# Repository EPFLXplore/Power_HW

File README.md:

# ERC_POWER_HW

This repository contains the KiCad design files for the power boards of the rover. The associated software can be found on the [ERC_POWER_SW](https://github.com/EPFLXplore/ERC_POWER_SW) repository.

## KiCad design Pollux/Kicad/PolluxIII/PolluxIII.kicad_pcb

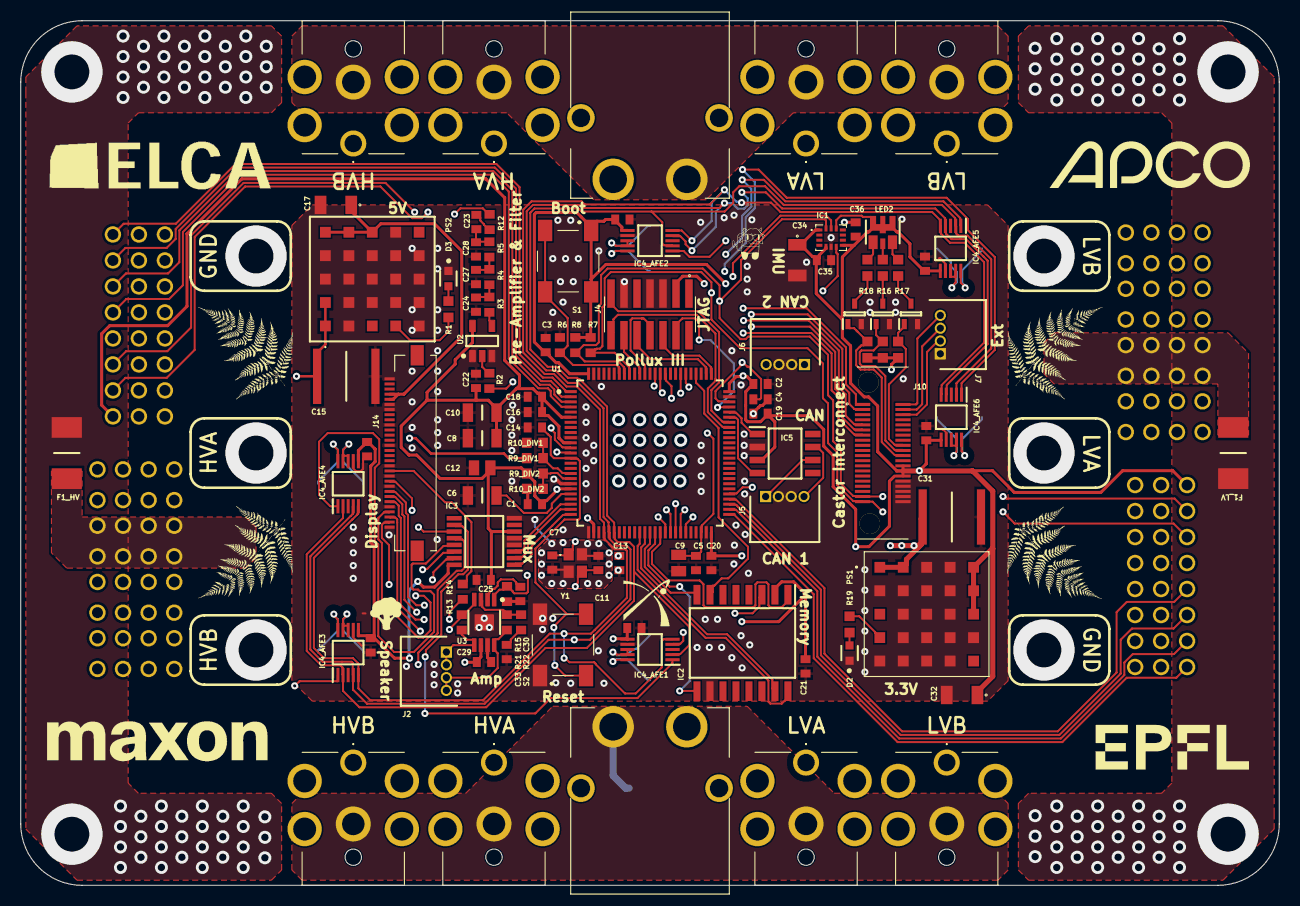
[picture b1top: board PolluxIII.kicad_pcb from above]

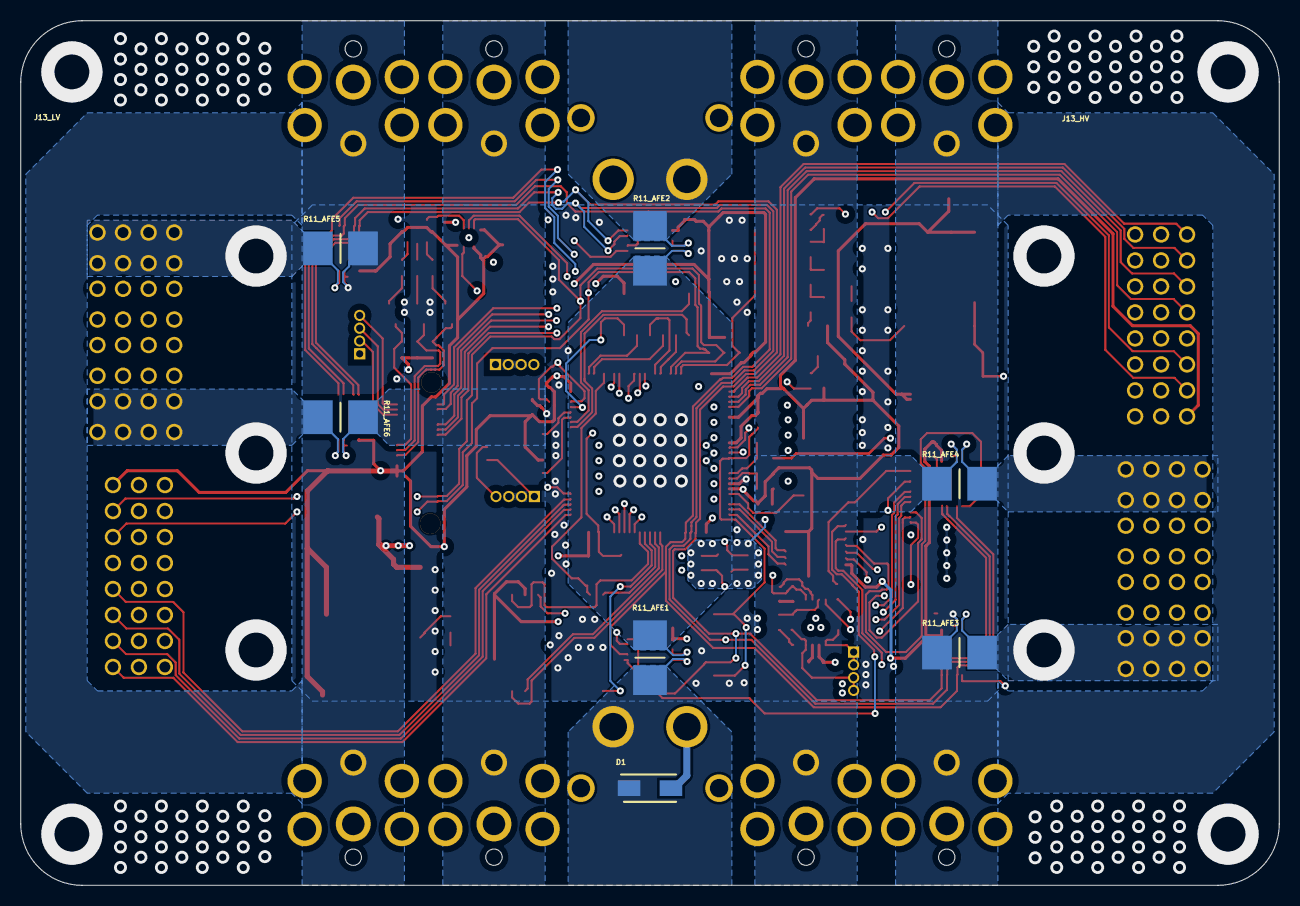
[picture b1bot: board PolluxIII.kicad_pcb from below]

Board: 4 copper layers, 123.0 x 84.5 mm, 118 parts (9 on the bottom side), 105 nets.

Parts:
C1, C2, C3, C4, C5, C13, C14, C16, C18, C19, C20, C21, C22, C25, C26_AFE1, C26_AFE2, C26_AFE3, C26_AFE4, C26_AFE5, C26_AFE6, C36: C0603C104K5RACTU; CAPC1608X95N
C6, C8, C10: C1206C105M5RECTU; CAPC3216X130N
C7, C11: CBR06C569B5GAC; CAPC1608X87N
C9: C0805C225K4REC7210; CAPC2012X140N
C12: C0805C475M4PACTU; CAPC2012X140N
C15, C31: C5750JB2A475M230KA; CAPC5750X310N
C17, C32: C1206C106K4RACTU; C1206
C23, C33: C0603C474K4PACTU; CAPC1608X95N
C24, C27, C28: C0603C472J5RACTU; CAPC1608X95N
C29: C0603C105K4RACTU; CAPC1608X95N
C30: C0603C224K8RAC7411; CAPC1608X95N
C34: C1206J225J4RACAUTO; C1206
C35: C0603C103K5RACTU; CAPC1608X95N
D1: BZG03C33-HM3-08; DIOM5127X229N
D2, D3: LS L29K-G1J2-1-Z; FP-LS_L29K-MFG
F1_HV, F1_LV: 0451020.MRL; FUSC6127X294N
IC1: ICM-42670-P; ICM42670P
IC2: MT25QL512ABB8ESF-0AAT; SOIC127P1032X265-16N
IC3: CD74HC137PWR; SOP65P640X120-16N
IC4_AFE1, IC4_AFE2, IC4_AFE3, IC4_AFE4, IC4_AFE5, IC4_AFE6: INA239AQDGSRQ1; SOP50P490X110-10N
IC5: SN65HVD232QDR; SOIC127P600X175-8N
J1, J3: XT60PW-M; XT60PWM
J2, J5, J6, J7: 53048-0450; SHDRRA4W35P0X125_1X4_675X550X350P
J4: FTSH-107-01-F-DV; FTSH-107-XX-YYY-DV
J10: ERF5-020-07.0-L-DV-K-TR; ERF5-020-XX.X-Y-DV-K-TR
J12_PWR1A1, J12_PWR1A2, J12_PWR1B1, J12_PWR1B2, J12_PWR2A1, J12_PWR2A2, J12_PWR2B1, J12_PWR2B2: PJ-082BH; PJ082BH
J13_HV, J13_LV: 46562-3001; 465623001
J14: 505110-3091; 5051103091
LED2: KRTBDWLM; KRTBDWLM3232T4U6JWAAABJ3R4S65V
PS1: RPMB3.3-3.0; RPMB5030
PS2: RPMB5.0-2.0; RPMB5020
Q5_LED_ST_B, Q5_LED_ST_G, Q5_LED_ST_R: DMN2004WK-7; SOT65P210X110-3N
R1, R19: CRCW06031K00JNEAC; RESC1608X55N
R2, R14: CRCW060333R0JNEAC; RESC1608X50N
R3, R4, R5: CRCW06031K00FKECC; RESC1608X50N
R6, R7, R8: CRCW06032K00JNEB; RESC1608X50N
R9_DIV1, R9_DIV2: TNPW0603100KBEEA; RESC1608X55N
R10_DIV1, R10_DIV2: TNPW06033K00BEEA; RESC1608X55N
R11_AFE1, R11_AFE2, R11_AFE3, R11_AFE4, R11_AFE5, R11_AFE6: PCS2512FR0010ET; RESC6430X90N
R12, R22: CRCW060310K2FKEA; RESC1608X50N
R13, R21: CRCW060320K0FKEAC; RESC1608X50N
R15: CRCW060347K0FKEAC; RESC1608X50N
R16: CRCW060320R0FKEAC; RESC1608X55N
R17, R18: CRCW060310R0JNEAC; RESC1608X55N
R20_LED_ST_B, R20_LED_ST_G, R20_LED_ST_R: CRCW060349K9FKEAC; RESC1608X55N
S1: BOOT; LL3301FF065QJ
S2: RESET; LL3301FF065QJ
U1: STM32H750VBT6; FP-LQFP100-1L-MFG
U2: SN74LVC1G125DBVR; DBV0005A_M
U3: TPA6205A1DGN; DGN0008D_N
Y1: NX3225SA-30.000M-STD-CSR-3; NX2520SA192MHzEXS00ACS05400

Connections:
3V3: C1.1, C2.1, C3.1, C8.2, C10.2, C12.1, C13.1, C16.1, C18.1, C19.1, C20.1, C21.1, C22.1, C25.1, C26_AFE1.2, C26_AFE2.2, C26_AFE3.2, C26_AFE4.2, C26_AFE5.2, C26_AFE6.2, C29.1, C32.1, C34.1, C35.1, C36.1, IC1.1, IC1.5, IC1.8, IC1.12, IC2.2, IC3.6, IC3.16, IC4_AFE1.6, IC4_AFE2.6, IC4_AFE3.6, IC4_AFE4.6, IC4_AFE5.6, IC4_AFE6.6, IC5.3, J4.3, J10.26, J10.28, J10.30, J13_HV.S17, J13_LV.S17, LED2.1, LED2.2, LED2.3, LED2.7, LED2.8, PS1.A5, PS1.B5, PS1.C5, R7.1, R8.1, R9_DIV2.1, R20_LED_ST_B.1, R20_LED_ST_G.1, R20_LED_ST_R.1, S1.1, S1.2, U1.6, U1.11, U1.20, U1.27, U1.50, U1.75, U1.100, U2.5, U3.6
+5: C17.1, J14.26, J14.27, PS2.A5, PS2.B5, PS2.C5
A1_C: J13_LV.S21, U1.54
A1_S: J13_LV.S23, U1.52
A2_C: J13_HV.S21, U1.4
A2_S: J13_HV.S23, U1.2
APD: J14.12, R14.1
APWM: J14.10, R2.1
B1_C: J13_LV.S22, U1.53
B1_S: J13_LV.S24, U1.51
B2_C: J13_HV.S22, U1.3
B2_S: J13_HV.S24, U1.1
BOOT: R6.2, S1.3, S1.4, U1.94
BYPASS: C30.2, U3.2
CANH: IC5.7, J5.4, J6.4
CANL: IC5.6, J5.1, J6.1
CAN_RX: IC5.4, U1.70
CAN_TX: IC5.1, U1.71
CAP: C4.1, C5.1, C9.2, U1.48, U1.73
CS1: IC3.15, IC4_AFE6.1
CS2: IC3.14, IC4_AFE5.1
CS3: IC3.13, IC4_AFE4.1
CS4: IC3.12, IC4_AFE3.1
CS5: IC3.11, IC4_AFE2.1
CS6: IC3.10, IC4_AFE1.1
DCS: J14.4, U1.41
DINT: J14.3, U1.45
DMISO: J14.7, U1.43
DMOSI: J14.6, U1.44
DRX: J4.13, U1.69
DSCK: J14.8, U1.42
DTX: J4.14, U1.68
FSYNC: IC1.7, U1.55
GND: C1.2, C2.2, C3.2, C4.2, C5.2, C6.1, C7.1, C8.1, C9.1, C10.1, C11.1, C12.2, C13.2, C14.2, C15.2, C16.2, C17.2, C18.2, C19.2, C20.2, C21.2, C22.2, C24.2, C25.2, C26_AFE1.1, C26_AFE2.1, C26_AFE3.1, C26_AFE4.1, C26_AFE5.1, C26_AFE6.1, C27.2, C28.2, C29.2, C30.1, C31.2, C32.2, C33.1, C34.2, C35.2, C36.2, D1.2, D2.1, D3.1, IC1.6, IC2.10, IC3.4, IC3.5, IC3.8, IC4_AFE1.7, IC4_AFE2.7, IC4_AFE3.7, IC4_AFE4.7, IC4_AFE5.7, IC4_AFE6.7, IC5.2, J1.2, J3.2, J4.5, J4.7, J4.11, J5.2, J5.3, J6.2, J6.3, J7.1, J10.32, J10.34, J10.36, J10.38, J10.40, J12_PWR1A1.2, J12_PWR1A2.2, J12_PWR1B1.2, J12_PWR1B2.2, J12_PWR2A1.2, J12_PWR2A2.2, J12_PWR2B1.2, J12_PWR2B2.2, J13_HV.P2, J13_HV.S20, J13_LV.P2, J13_LV.S20, J14.1, J14.5, J14.9, J14.11, J14.13, J14.17, J14.21, J14.24, J14.25, J14.30, PS1.A3, PS1.A4, PS1.B1, PS1.B2, PS1.B3, PS1.B4, PS1.C2, PS1.C3, PS1.C4, PS1.D2, PS1.D3, PS1.D4, PS1.D5, PS1.E1, PS1.E2, PS1.E3, PS1.E4, PS2.A3, PS2.A4, PS2.B1, PS2.B2, PS2.B3, PS2.B4, PS2.C2, PS2.C3, PS2.C4, PS2.D2, PS2.D3, PS2.D4, PS2.D5, PS2.E1, PS2.E2, PS2.E3, PS2.E4, Q5_LED_ST_B.2, Q5_LED_ST_G.2, Q5_LED_ST_R.2, R6.1, R10_DIV1.2, R10_DIV2.2, R15.1, S2.1, S2.2, U1.10, U1.19, U1.26, U1.49, U1.74, U1.99, U2.1, U2.3, U3.7, U3.9, Y1.2, Y1.4
GPIO0: J7.4, J10.2
GPIO1: J7.3, J10.4
GPIO2: J7.2, J10.6
HSE_IN: C7.2, U1.12, Y1.1
HSE_OUT: C11.2, U1.13, Y1.3
HVA: IC4_AFE4.10, J13_HV.P4, R11_AFE4.1
HVB: IC4_AFE3.10, J13_HV.P1, R11_AFE3.1
JTCK: J4.6, U1.76
JTDI: J4.10, U1.77
JTDO: J4.8, U1.89
JTMS: J4.4, U1.72
JTRST: J4.12, U1.90
LVA: IC4_AFE6.10, J13_LV.P4, R11_AFE6.1
LVB: IC4_AFE5.10, J13_LV.P1, R11_AFE5.1
MISO: IC4_AFE1.4, IC4_AFE2.4, IC4_AFE3.4, IC4_AFE4.4, IC4_AFE5.4, IC4_AFE6.4, U1.30
MOSI: IC4_AFE1.2, IC4_AFE2.2, IC4_AFE3.2, IC4_AFE4.2, IC4_AFE5.2, IC4_AFE6.2, U1.31
NRST: C14.1, IC2.3, J14.2, S2.3, S2.4, U1.14
NetC6_2: C6.2, U1.21
NetC23_1: C23.1, R12.1
NetC23_2: C23.2, C28.1, R5.1
NetC24_1: C24.1, R3.1, R4.2
NetC27_1: C27.1, R4.1, R5.2
NetC33_2: C33.2, R22.2
NetD2_2: D2.2, R19.1
NetD3_2: D3.2, R1.1
NetF1_HV_2: F1_HV.2, J13_HV.P3
NetF1_LV_2: F1_LV.2, J13_LV.P3
NetJ2_1: J2.1, J2.2, R13.1, U3.5
NetJ2_3: J2.3, J2.4, R21.1, U3.8
NetJ10_18: J10.18, Q5_LED_ST_G.1, R20_LED_ST_G.2
NetJ10_20: J10.20, Q5_LED_ST_R.1, R20_LED_ST_R.2
NetJ10_22: J10.22, Q5_LED_ST_B.1, R20_LED_ST_B.2
NetLED2_4: LED2.4, R18.2
NetLED2_5: LED2.5, R16.2
NetLED2_6: LED2.6, R17.2
NetPS1_D1: PS1.D1, R19.2
NetPS2_D1: PS2.D1, R1.2
NetQ5_LED_ST_B_3: Q5_LED_ST_B.3, R18.1
NetQ5_LED_ST_G_3: Q5_LED_ST_G.3, R17.1
NetQ5_LED_ST_R_3: Q5_LED_ST_R.3, R16.1
NetR2_2: R2.2, U2.2
NetR3_2: R3.2, U2.4
NetR9_DIV1_2: R9_DIV1.2, R10_DIV1.1, U1.17
NetR9_DIV2_2: R9_DIV2.2, R10_DIV2.1, U1.18
NetR12_2: R12.2, R13.2, U3.4
NetR21_2: R21.2, R22.1, U3.3
OHVA: IC4_AFE4.8, IC4_AFE4.9, J12_PWR2A1.1, J12_PWR2A2.1, R11_AFE4.2
OHVB: IC4_AFE3.8, IC4_AFE3.9, J12_PWR2B1.1, J12_PWR2B2.1, R11_AFE3.2
OLVA: IC4_AFE6.8, IC4_AFE6.9, J12_PWR1A1.1, J12_PWR1A2.1, R11_AFE6.2
OLVB: IC4_AFE5.8, IC4_AFE5.9, J12_PWR1B1.1, J12_PWR1B2.1, R11_AFE5.2
QSPI0: IC2.15, U1.37
QSPI1: IC2.8, U1.38
QSPI2: IC2.9, U1.39
QSPI3: IC2.1, U1.40
QSPICK: IC2.16, U1.36
QSPICS: IC2.7, U1.79
SBUS0: J10.1, U1.86
SBUS1: J10.3, U1.87
SBUS4: J10.9, U1.85
SBUS5: J10.11, U1.81
SBUS6: J10.13, U1.82
SCK: IC4_AFE1.5, IC4_AFE2.5, IC4_AFE3.5, IC4_AFE4.5, IC4_AFE5.5, IC4_AFE6.5, U1.29
SCL: IC1.13, J10.39, J13_HV.S19, J13_LV.S19, R7.2, U1.92
SDA: IC1.14, J10.37, J13_HV.S18, J13_LV.S18, R8.2, U1.93
SPI_A0: IC3.1, U1.25
SPI_A1: IC3.2, U1.24
SPI_A2: IC3.3, U1.23
V_BAT: D1.1, IC4_AFE1.10, J1.1, R11_AFE1.1
V_IN: C15.1, C31.1, F1_HV.1, F1_LV.1, IC4_AFE1.8, IC4_AFE1.9, IC4_AFE2.10, PS1.A1, PS1.A2, PS2.A1, PS2.A2, R9_DIV1.1, R11_AFE1.2, R11_AFE2.1
V_OUT: IC4_AFE2.8, IC4_AFE2.9, J3.1, R11_AFE2.2
nSHDN: R14.2, R15.2, U3.1

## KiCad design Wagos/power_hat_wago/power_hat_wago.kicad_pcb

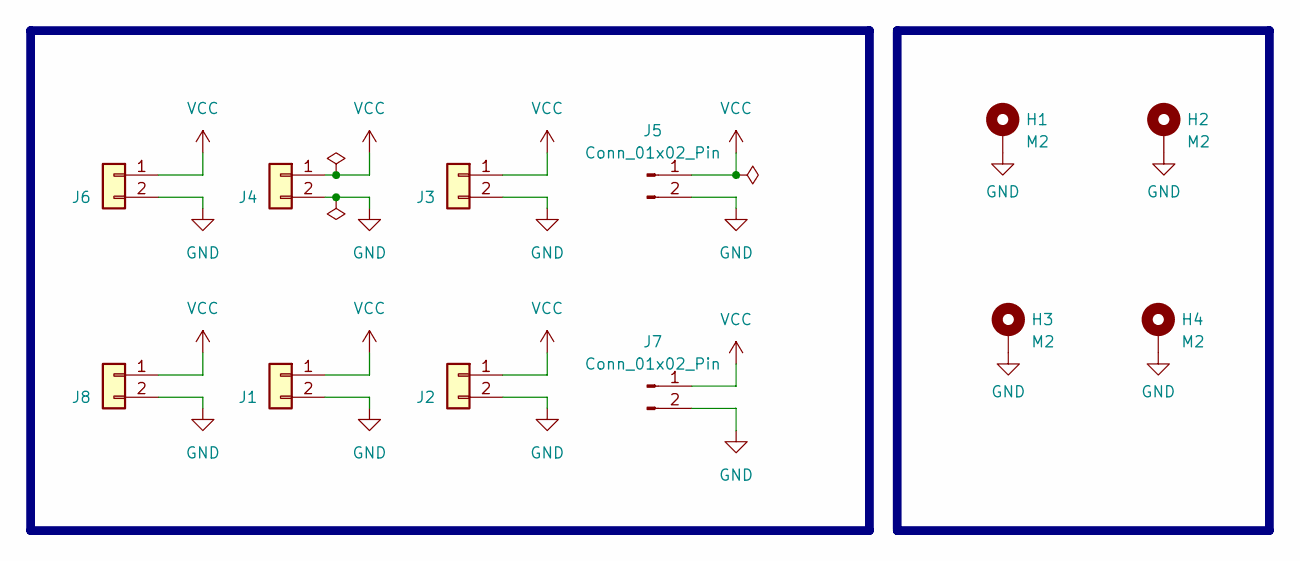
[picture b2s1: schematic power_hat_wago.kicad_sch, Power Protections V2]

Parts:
H1, H2, H3, H4: M2; MountingHole_3.2mm_M3_Pad_Via
J1, J2, J3, J4, J6, J8: XT30PW-M/Terminal block; AMASS_XT30PW-M_1x02_P2.50mm_Horizontal; Manufacturer_Part_Number XT30PW-M
J5: Conn_01x02_Pin; AMASS_XT60PW-M_1x02_P7.20mm_Horizontal
J7: Conn_01x02_Pin; AMASS_XT60PW-F_1x02_P7.20mm_Horizontal

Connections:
GND: H1.1 (1_1), H2.1 (1_1), H3.1 (1_1), H4.1 (1_1), J1.2, J2.2, J3.2, J4.2, J5.2, J6.2, J7.2, J8.2
VCC: J1.1, J2.1, J3.1, J4.1, J5.1, J6.1, J7.1, J8.1

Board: 4 copper layers, 12 parts (0 on the bottom side), 2 nets, no tracks yet.

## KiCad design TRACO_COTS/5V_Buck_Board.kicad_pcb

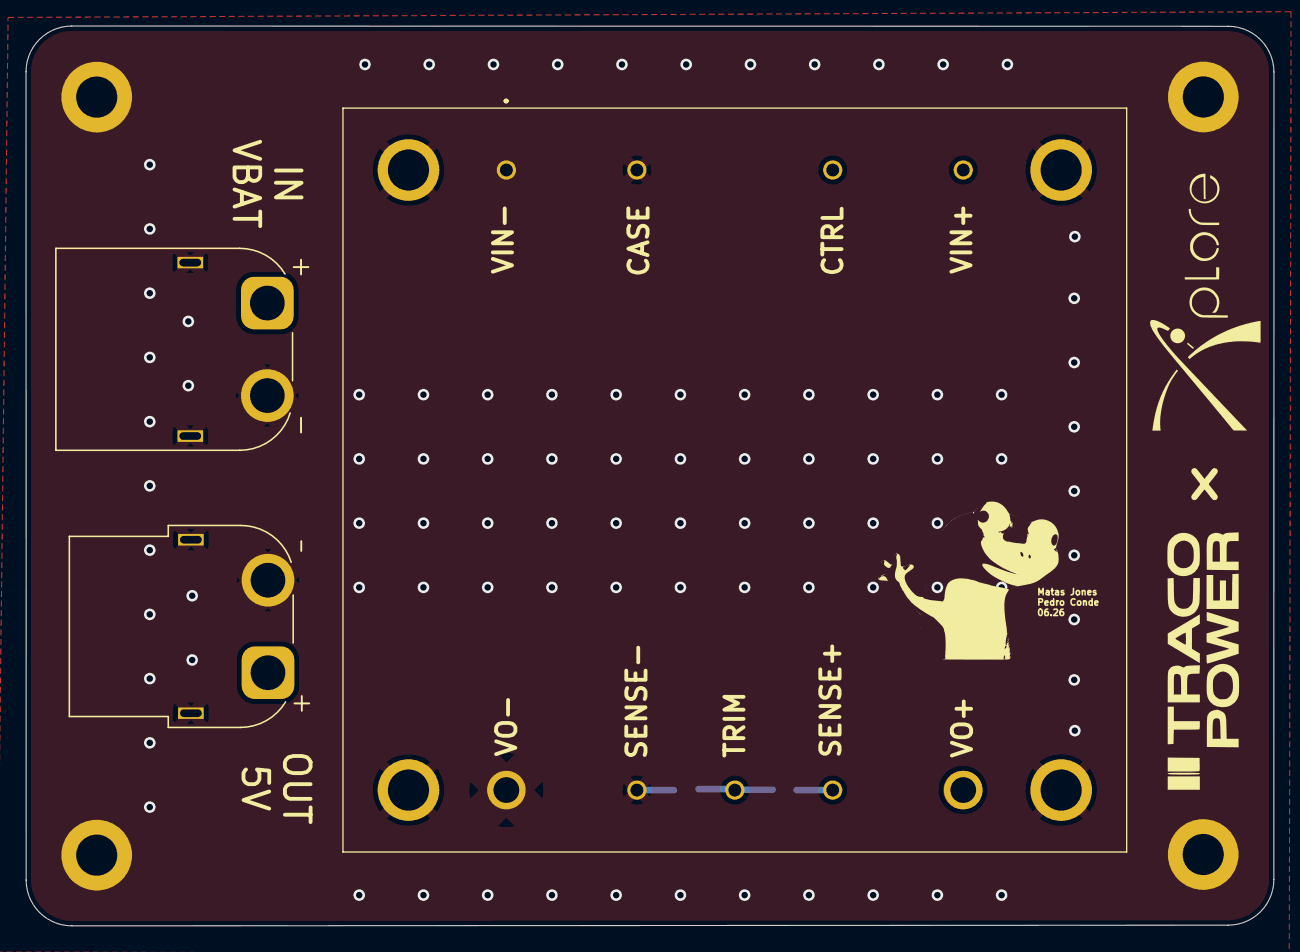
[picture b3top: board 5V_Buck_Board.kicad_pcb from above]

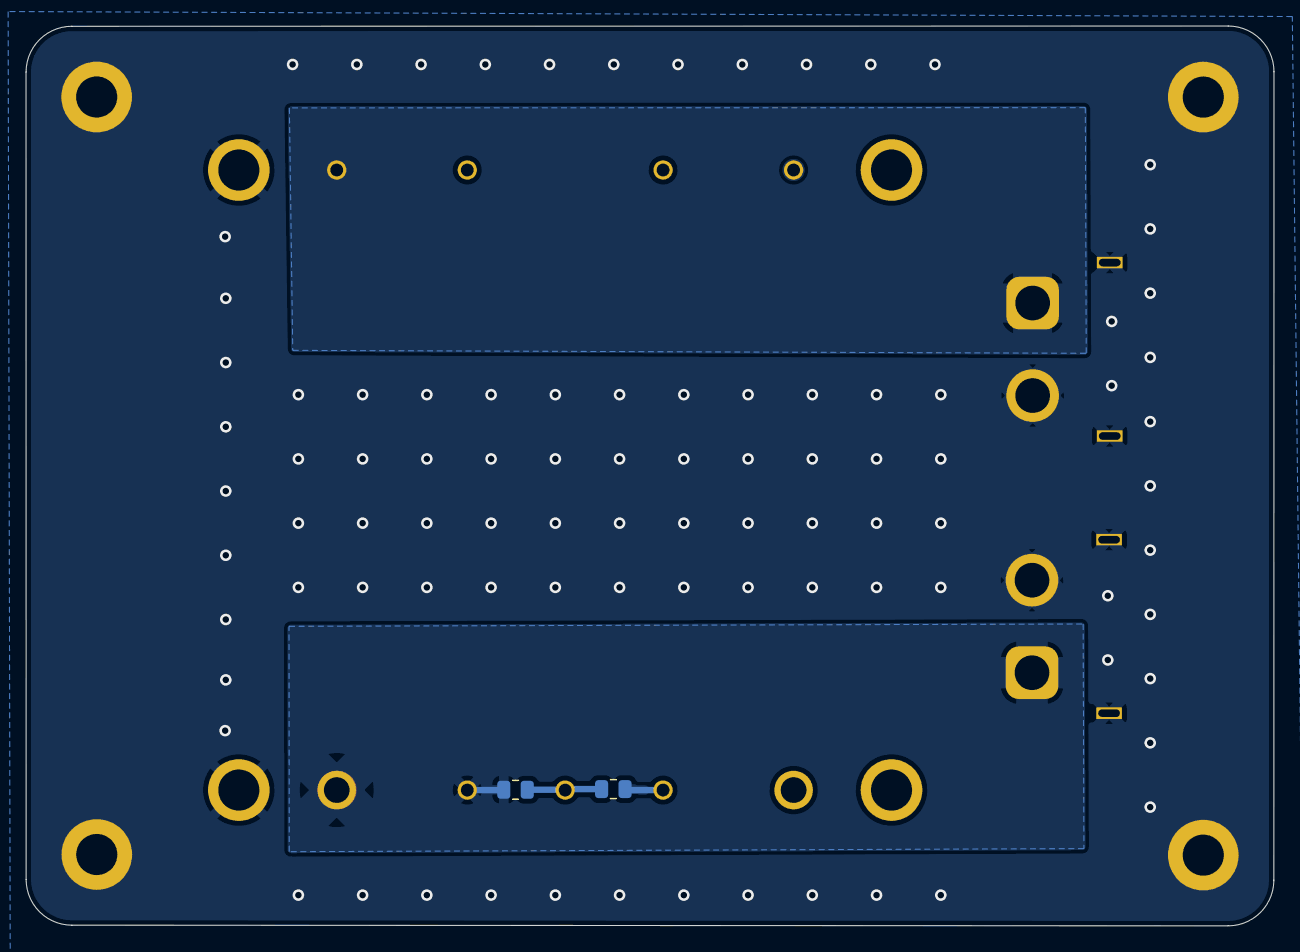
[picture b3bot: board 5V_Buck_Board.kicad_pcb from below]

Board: 2 copper layers, 97.1 x 70.0 mm, 9 parts (2 on the bottom side), 4 nets.

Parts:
H1, H2, H3, H4: MountingHole_Pad; MountingHole_3.2mm_M3_ISO14580_Pad
J1: XT60PW-M; AMASS_XT60PW-M_1x02_P7.20mm_Horizontal
J2: XT60PW-F; AMASS_XT60PW-F_1x02_P7.20mm_Horizontal
PS1: TEP_100-2411WIR; TEP1002411WIR
R1, R2: NM; R_0805_2012Metric

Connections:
GND: H1.1, H2.1, H3.1, H4.1, J1.2, J1.MH1, J1.MH2, J2.2, J2.MH1, J2.MH2, PS1.1 (-VIN(GND)), PS1.2 (CASE), PS1.5 (-VOUT), PS1.6 (-SENSE), PS1.MH1, PS1.MH2, PS1.MH3, PS1.MH4, R2.2
unnamed: J2.1, PS1.8 (+SENSE), PS1.9 (+VOUT), R1.1
unnamed: J1.1, PS1.4 (+VIN(VCC))
unnamed: PS1.7 (TRIM), R1.2, R2.1

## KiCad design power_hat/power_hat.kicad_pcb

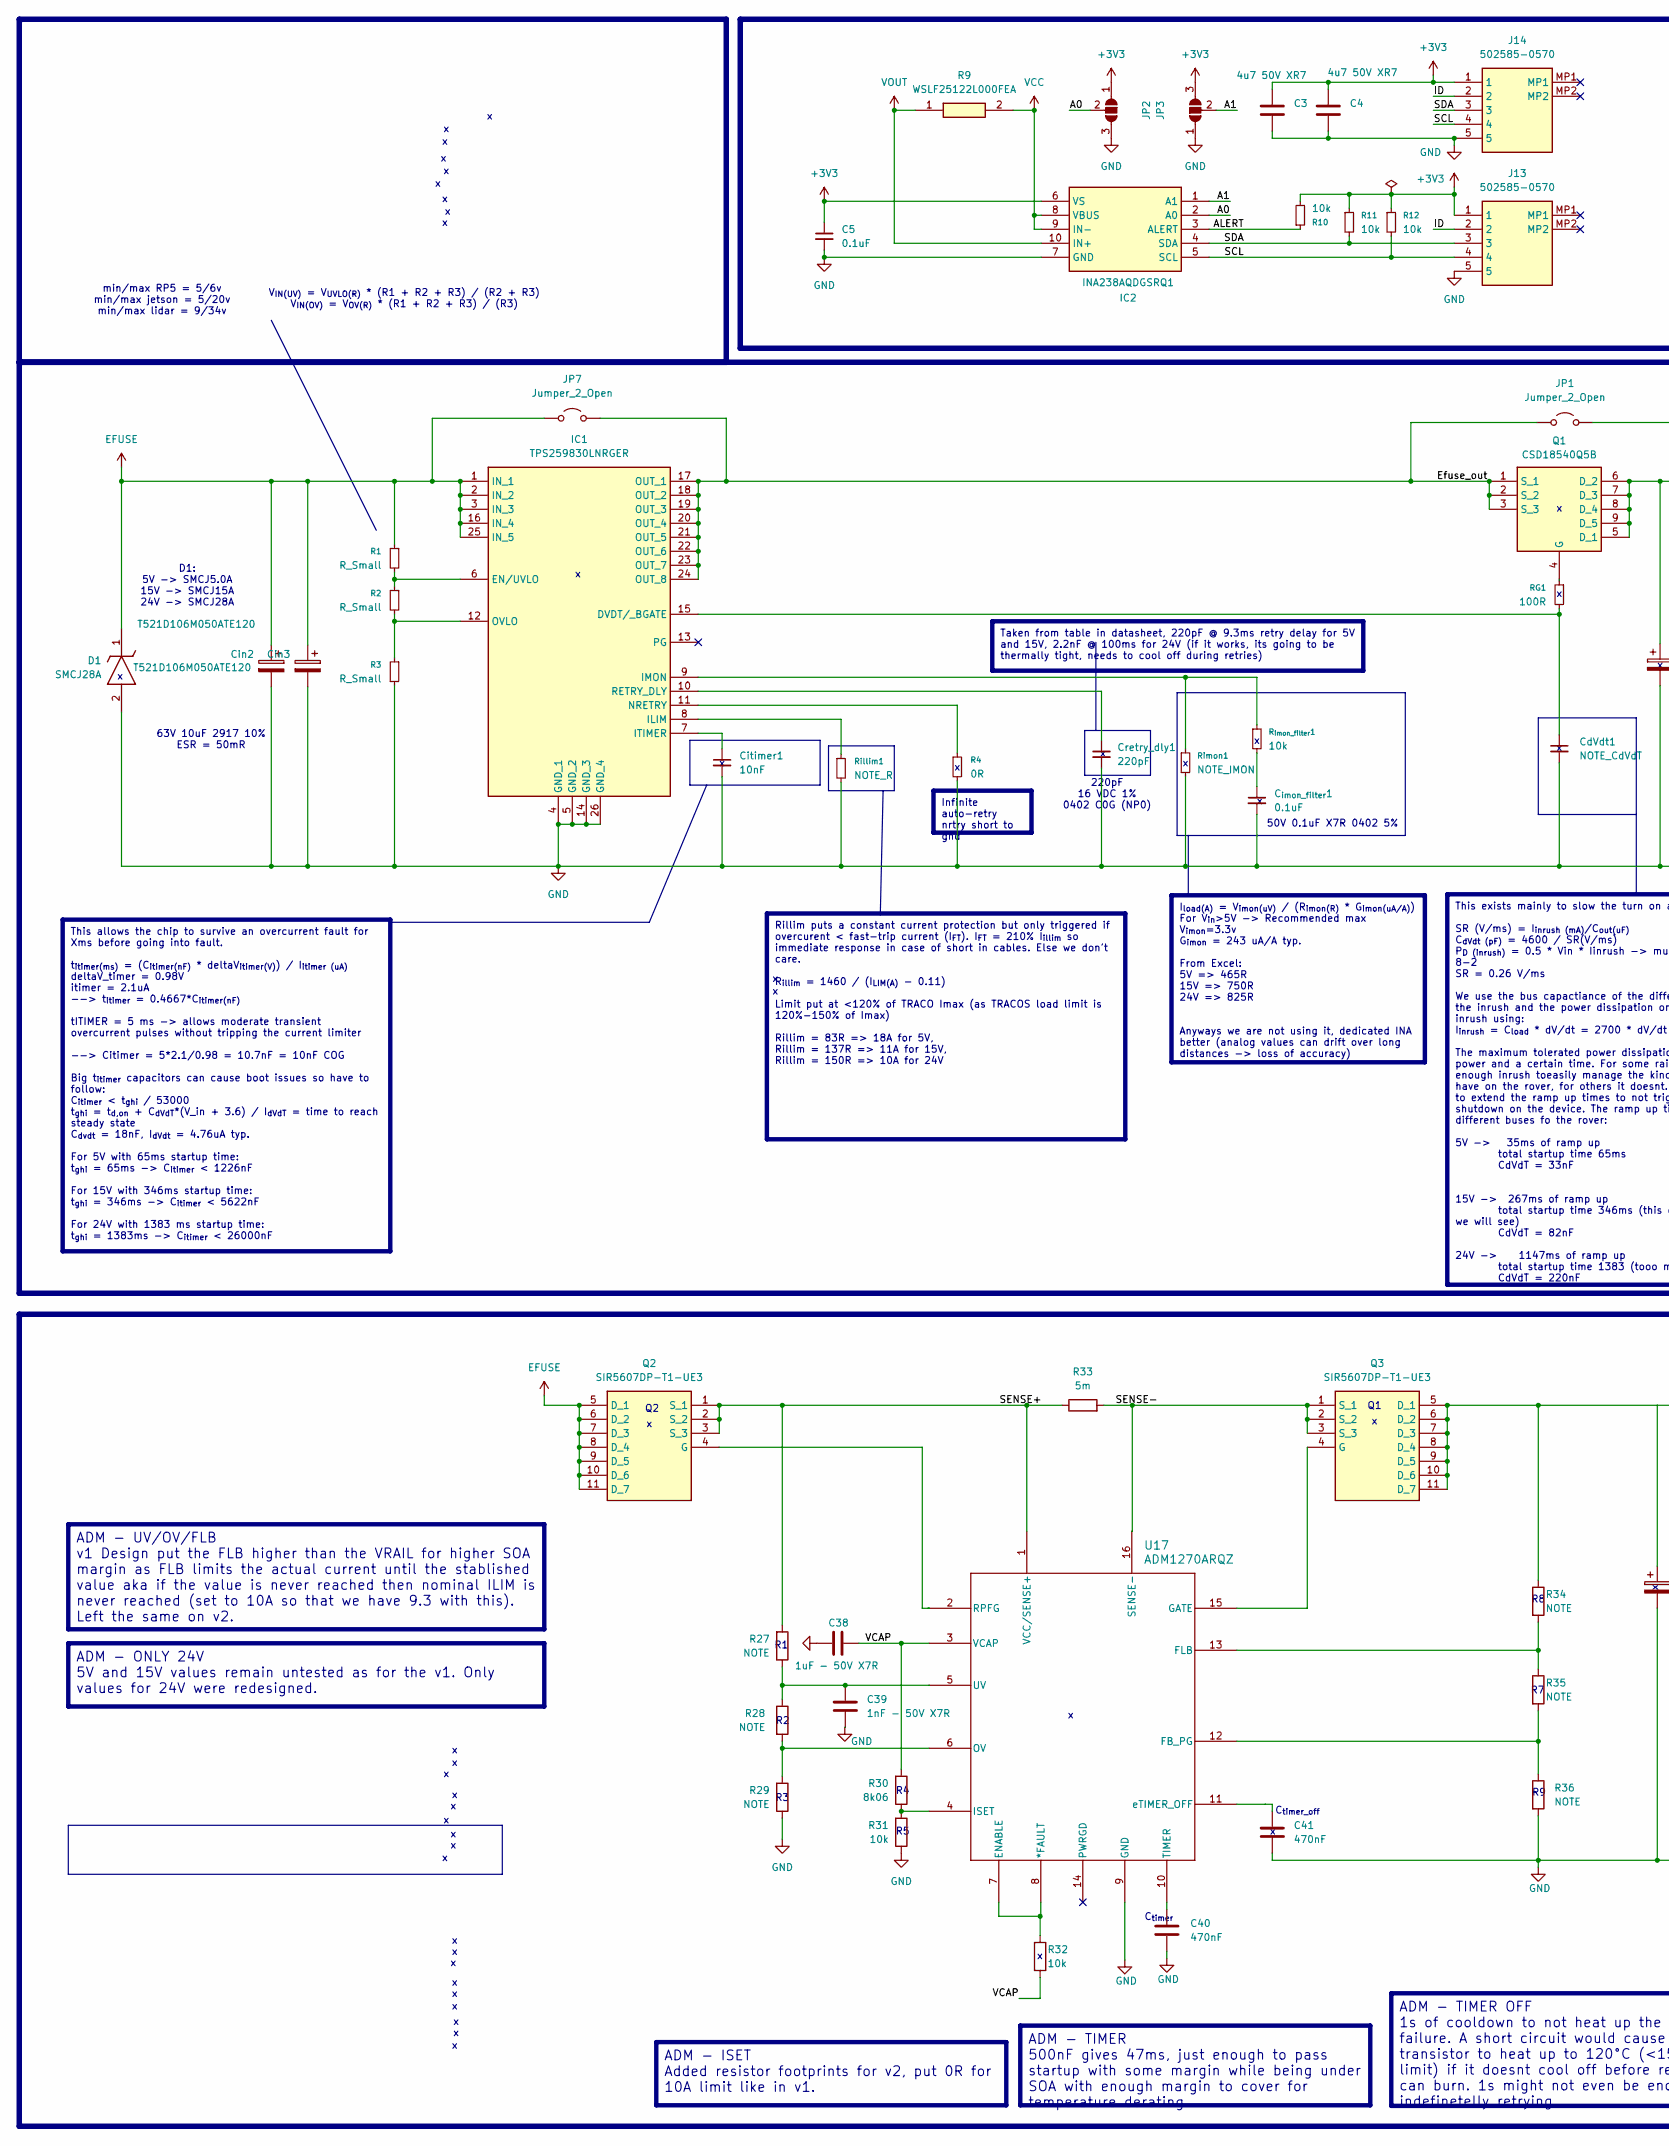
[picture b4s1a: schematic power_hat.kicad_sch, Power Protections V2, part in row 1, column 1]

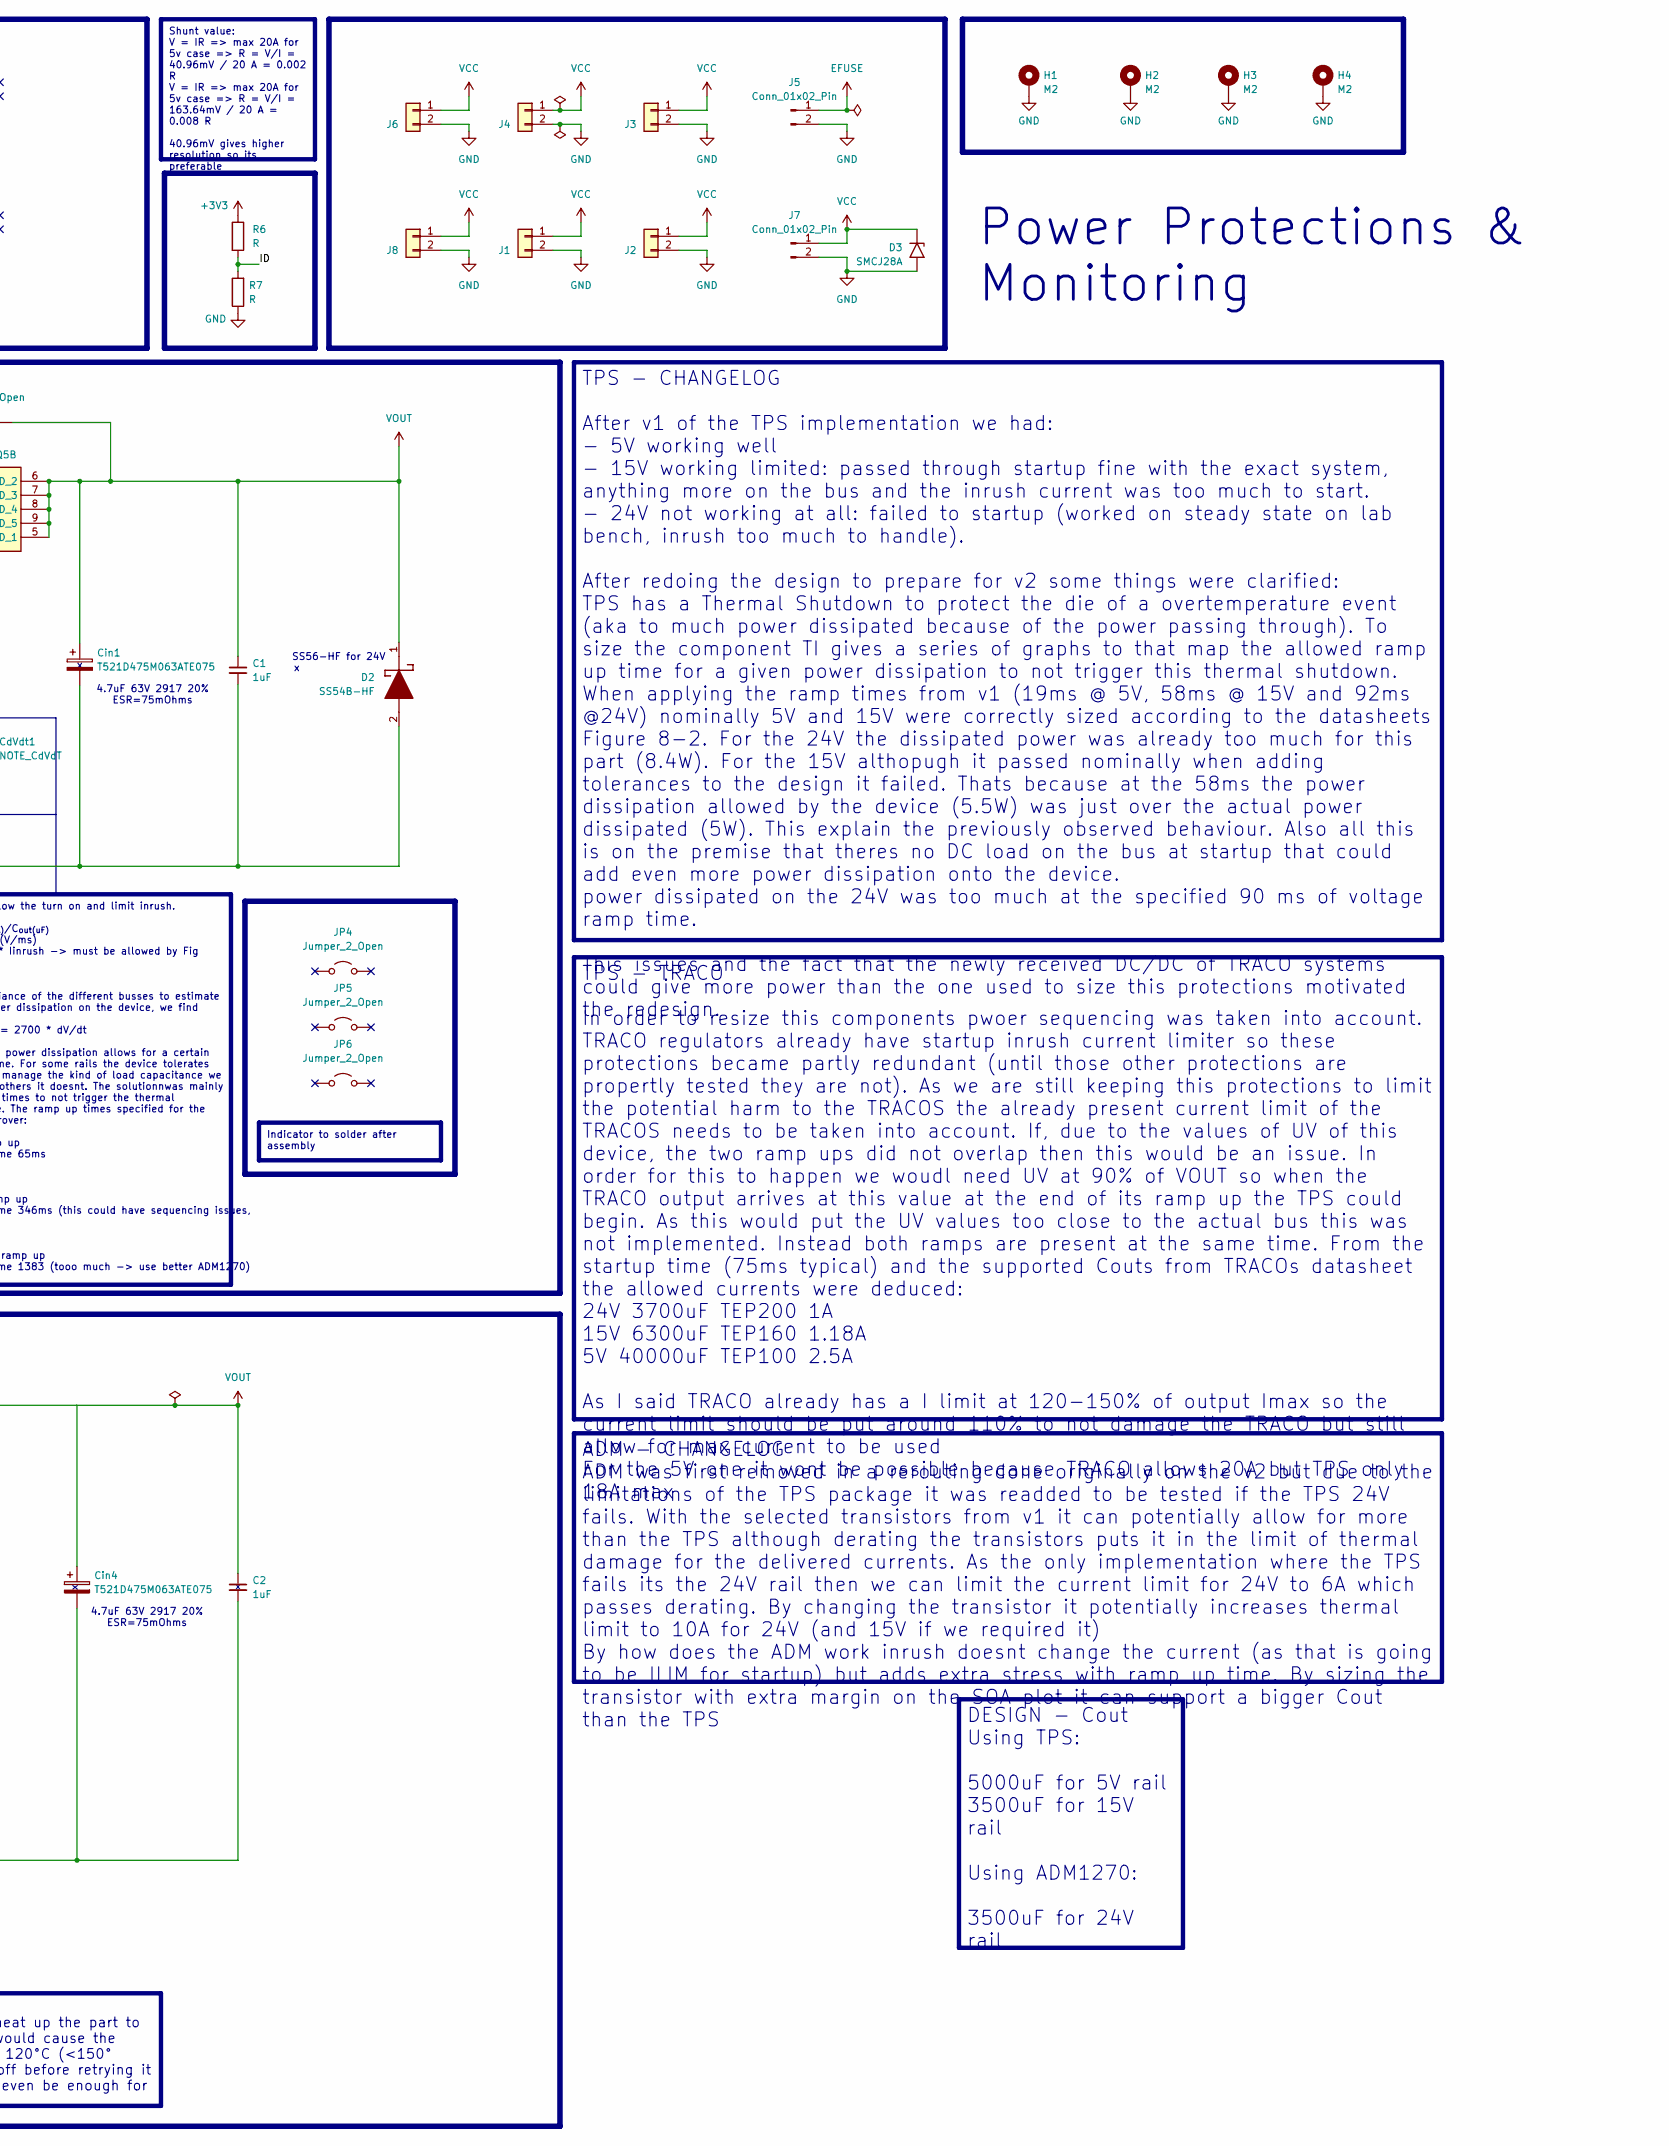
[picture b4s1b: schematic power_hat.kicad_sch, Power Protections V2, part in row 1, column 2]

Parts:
C1, C2: 1uF; C_0805_2012Metric_Pad1.18x1.45mm_HandSolder
C3, C4: 4u7 50V XR7; C_0603_1608Metric
C5: 0.1uF; C_0402_1005Metric_Pad0.74x0.62mm_HandSolder; Mouser Ref 581-04025C104JAT2A
C38: 1uF - 50V X7R; C_0805_2012Metric; JLCPCB C28323
C39: 1nF - 50V X7R; C_0805_2012Metric; JLCPCB C46653
C40, C41: 470nF; C_0805_2012Metric; JLCPCB C1711
C_{imon_filter}1: 0.1uF; C_0402_1005Metric_Pad0.74x0.62mm_HandSolder; Mouser Ref 581-04025C104JAT2A
CdVdt1: NOTE_CdVdT; C_1206_3216Metric_Pad1.33x1.80mm_HandSolder
Cin1, Cin4: T521D475M063ATE075; T521D; Mouser Ref 80-T521D475M63ATE075
Cin2, Cin3: T521D106M050ATE120; T521D; Mouser Ref 80-T543X106K63AHW50
Citimer1: 10nF; C_0402_1005Metric_Pad0.74x0.62mm_HandSolder; Mouser Ref 81-GRM1555CYA103GE1J
Cretry_dly1: 220pF; C_0402_1005Metric_Pad0.74x0.62mm_HandSolder
D1: SMCJ28A; SMCJ50A; Mouser Ref 621-3.0SMCJ28A-13
D2: SS54B-HF; DIOM5235X244N; Mouser Part Number 750-SS54B-HF
D3: SMCJ28A; D_SMA; Mouser Ref 621-3.0SMCJ28A-13
H1, H2, H3, H4: M2; MountingHole_2.2mm_M2_Pad_Via
IC1: TPS259830LNRGER; Mouser Part Number 595-TPS259830LNRGER
IC2: INA238AQDGSRQ1; SOP50P490X110-10N; Mouser Part Number 595-INA238AQDGSRQ1
J1, J2, J3, J4, J6, J8: XT30PW-M/Terminal block; AMASS_XT30PW-M_1x02_P2.50mm_Horizontal
J5: Conn_01x02_Pin; AMASS_XT60PW-M_1x02_P7.20mm_Horizontal
J7: Conn_01x02_Pin; AMASS_XT60PW-F_1x02_P7.20mm_Horizontal
J13, J14: 502585-0570; 5025850570; Mouser Part Number 538-502585-0570
JP1, JP4, JP5, JP6, JP7: Jumper_2_Open; SolderJumper-2_P1.3mm_Open_RoundedPad1.0x1.5mm
JP2, JP3: SolderJumper-3_P1.3mm_Open_RoundedPad1.0x1.5mm
Q1: CSD18540Q5B; Mouser Part Number 595-CSD18540Q5B
Q2, Q3: SIR5607DP-T1-UE3; SIRA14DPT1GE3; Manufacturer_Part_Number SIR5607DP-T1-UE3
R1, R2, R3: R_Small; R_0805_2012Metric_Pad1.20x1.40mm_HandSolder
R4: 0R; R_0402_1005Metric_Pad0.72x0.64mm_HandSolder; Mouser Ref 594-MCS0402MZ0000ZE0
R6, R7: R; R_0603_1608Metric
R9: WSLF25122L000FEA; RESC6430X38N; Mouser Part Number 71-WSLF25122L000FEA
R10, R11, R12: 10k; R_0402_1005Metric_Pad0.72x0.64mm_HandSolder; Mouser Ref 71-CRCW040210K0FHEDP
R27: NOTE; R_0805_2012Metric; JLCPCB C17598
R28: NOTE; R_0805_2012Metric; JLCPCB C17677
R29: NOTE; R_0805_2012Metric; JLCPCB C17414
R30: 8k06; R_0805_2012Metric; JLCPCB C17598
R31: 10k; R_0805_2012Metric; JLCPCB C17598
R32: 10k; R_0805_2012Metric; JLCPCB C17631
R33: 5m; R_2512_6332Metric; Mfr_Part_Number WPB2512QLR005FYR; JLCPCB C705607
R34: NOTE; R_0805_2012Metric; JLCPCB C104550
R35: NOTE; R_0805_2012Metric; JLCPCB C104036
R36: NOTE; R_0805_2012Metric; JLCPCB C2828855
RG1: 100R; R_0402_1005Metric; Mouser Ref 710-560112110022
R_{imon_filter}1: 10k; R_0402_1005Metric_Pad0.72x0.64mm_HandSolder; Mouser Ref 71-CRCW040210K0FHEDP
Rillim1: NOTE_R; R_0402_1005Metric_Pad0.72x0.64mm_HandSolder
Rimon1: NOTE_IMON; R_0402_1005Metric_Pad0.72x0.64mm_HandSolder
U17: ADM1270ARQZ; SSOP-16_3.9x4.9mm_P0.635mm; Voltage high voltage; Digikey ADM1270ARQZ

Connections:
+3V3: C3.1, C4.1, C5.1, IC2.6 (VS), J13.1, J14.1, JP2.1 (A), JP3.3 (B), R6.1, R10.2, R11.1, R12.1
/A0: IC2.2 (A0), JP2.2 (C)
/A1: IC2.1 (A1), JP3.2 (C)
/ALERT: IC2.3 (ALERT), R10.1
/Efuse_out: IC1.17 (OUT_1), IC1.18 (OUT_2), IC1.19 (OUT_3), IC1.20 (OUT_4), IC1.21 (OUT_5), IC1.22 (OUT_6), IC1.23 (OUT_7), IC1.24 (OUT_8), JP1.1 (A), JP7.2 (B), Q1.1 (S_1), Q1.2 (S_2), Q1.3 (S_3)
/ID: J13.2, J14.2, R6.2, R7.2
/SCL: IC2.5 (SCL), J13.4, J14.4, R12.2
/SDA: IC2.4 (SDA), J13.3, J14.3, R11.2
/SENSE+: Q2.1 (S_1), Q2.2 (S_2), Q2.3 (S_3), R27.2, R33.1, U17.1 (VCC/SENSE+)
/SENSE-: Q3.1 (S_1), Q3.2 (S_2), Q3.3 (S_3), R33.2, U17.16 (SENSE-)
/VCAP: C38.1, R30.2, R32.2, U17.3 (VCAP)
EFUSE: Cin2.1, Cin3.1, D1.1 (K), IC1.1 (IN_1), IC1.2 (IN_2), IC1.3 (IN_3), IC1.16 (IN_4), IC1.25 (IN_5), J5.1, JP7.1 (A), Q2.5 (D_1), Q2.6 (D_2), Q2.7 (D_3), Q2.8 (D_4), Q2.9 (D_5), Q2.10 (D_6), Q2.11 (D_7), R1.1
GND: C1.2, C2.2, C3.2, C4.2, C5.2, C38.2, C39.2, C40.2, C41.2, C_{imon_filter}1.2, CdVdt1.2, Cin1.2, Cin2.2, Cin3.2, Cin4.2, Citimer1.2, Cretry_dly1.2, D1.2 (A), D2.2 (A), D3.2 (A2), H1.1 (1_1), H2.1 (1_1), H3.1 (1_1), H4.1 (1_1), IC1.4 (GND_1), IC1.5 (GND_2), IC1.14 (GND_3), IC1.26 (GND_4), IC2.7 (GND), J1.2, J2.2, J3.2, J4.2, J5.2, J6.2, J7.2, J8.2, J13.5, J14.5, JP2.3 (B), JP3.1 (A), R3.2, R4.2, R7.1, R29.1, R31.1, R36.2, Rillim1.2, Rimon1.2, U17.9 (GND)
unnamed: C_{imon_filter}1.1, R_{imon_filter}1.2
unnamed: CdVdt1.1, IC1.15 (DVDT/_BGATE), RG1.2
unnamed: IC1.6 (EN/UVLO), R1.2, R2.1
unnamed: IC1.8 (ILIM), Rillim1.1
unnamed: IC1.9 (IMON), R_{imon_filter}1.1, Rimon1.1
unnamed: Citimer1.1, IC1.7 (ITIMER)
unnamed: IC1.11 (NRETRY), R4.1
unnamed: IC1.12 (OVLO), R2.2, R3.1
unnamed: Cretry_dly1.1, IC1.10 (RETRY_DLY)
unnamed: Q1.4 (G), RG1.1
unnamed: Q2.4 (G), U17.2 (RPFG)
unnamed: Q3.4 (G), U17.15 (GATE)
unnamed: R32.1, U17.7 (ENABLE), U17.8 (*FAULT)
unnamed: R35.2, R36.1, U17.12 (FB_PG)
unnamed: R34.2, R35.1, U17.13 (FLB)
unnamed: R30.1, R31.2, U17.4 (ISET)
unnamed: R28.2, R29.2, U17.6 (OV)
unnamed: C40.1, U17.10 (TIMER)
unnamed: C39.1, R27.1, R28.1, U17.5 (UV)
unnamed: C41.1, U17.11 (eTIMER_OFF)
VCC: D3.1 (A1), IC2.8 (VBUS), IC2.9 (IN-), J1.1, J2.1, J3.1, J4.1, J6.1, J7.1, J8.1, R9.2
VOUT: C1.1, C2.1, Cin1.1, Cin4.1, D2.1 (K), IC2.10 (IN+), JP1.2 (B), Q1.5 (D_1), Q1.6 (D_2), Q1.7 (D_3), Q1.8 (D_4), Q1.9 (D_5), Q3.5 (D_1), Q3.6 (D_2), Q3.7 (D_3), Q3.8 (D_4), Q3.9 (D_5), Q3.10 (D_6), Q3.11 (D_7), R9.1, R34.1

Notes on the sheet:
C_{timer_off}
220pF 16 VDC 1% 0402 C0G (NP0)
D1: 5V -> SMCJ5.0A 15V -> SMCJ15A 24V -> SMCJ28A
4.7uF 63V 2917 20% ESR=75mOhms
C_{timer}
63V 10uF 2917 10% ESR = 50mR
V_{IN(UV)} = V_{UVLO(R)} * (R1 + R2 + R3) / (R2 + R3) V_{IN(OV)} = V_{OV(R)} * (R1 + R2 + R3) / (R3)
min/max RP5 = 5/6v min/max jetson = 5/20v min/max lidar = 9/34v
50V 0.1uF X7R 0402 5%
SS56-HF for 24V
ADM - TIMER OFF 1s of cooldown to not heat up the part to failure. A short circuit would cause the transistor to heat up to 120°C (<150° limit) if it doesnt cool off before retrying it can burn. 1s might not even be enough for indefinetelly retrying
This exists mainly to slow the turn on and limit inrush. SR (V/ms) = I_{inrush (mA)}/C_{out(uF)} C_{dVdt (pF)} = 4600 / SR(V/ms) P_{D (inrush)} = 0.5 * Vin * Iinrush -> must be allowed by Fig 8-2 SR = 0.26 V/ms We use the bus capactiance of the different busses to estimate the inrush and the power 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
DESIGN - Cout Using TPS: 5000uF for 5V rail 3500uF for 15V rail Using ADM1270: 3500uF for 24V rail
ADM - CHANGELOG ADM was first removed in a rerouting done originally on the v2 but due to the limitations of the TPS package it was readded to be tested if the TPS 24V fails. With the selected transistors from v1 it can potentially allow for more than the TPS although derating the transistors puts 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
TPS - TRACO In order to resize this components pwoer sequencing was taken into account. TRACO regulators already have startup inrush current limiter so these protections became partly redundant (until those other protections are propertly tested they are not). As we are still keeping this protectio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
Taken from table in datasheet, 220pF @ 9.3ms retry delay for 5V and 15V, 2.2nF @ 100ms for 24V (if it works, its going to be thermally tight, needs to cool off during retries)
Shunt value: V = IR => max 20A for 5v case => R = V/I = 40.96mV / 20 A = 0.002 R V = IR => max 20A for 5v case => R = V/I = 163.64mV / 20 A = 0.008 R 40.96mV gives higher resolution so its preferable
ADM - UV/OV/FLB v1 Design put the FLB higher than the VRAIL for higher SOA margin as FLB limits the actual current until the stablished value aka if the value is never reached then nominal ILIM is never reached (set to 10A so that we have 9.3 with this). Left the same on v2.
ADM - ONLY 24V 5V and 15V values remain untested as for the v1. Only values for 24V were redesigned.
I_{load(A)} = V_{imon(uV)} / (R_{imon(R)} * G_{imon(uA/A)}) For V_{in}>5V -> Recommended max V_{imon}=3.3v G_{imon} = 243 uA/A typ. From Excel: 5V => 465R 15V => 750R 24V => 825R Anyways we are not using it, dedicated INA better (analog values can drift over long distances -> loss of accuracy)
Power Protections & Monitoring
TPS - CHANGELOG After v1 of the TPS implementation we had: - 5V working well - 15V working limited: passed through startup fine with the exact system, anything more on the bus and the inrush current was too much to start. - 24V not working at all: failed to startup (worked on steady state on lab be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
Indicator to solder after assembly
Rillim puts a constant current protection but only triggered if overcurent < fast-trip current (I_{FT}). I_{FT} = 210% I_{illim} so immediate response in case of short in cables. Else we don't care. R_{illim} = 1460 / (I_{LIM(A)} - 0.11) Limit put at <120% of TRACO Imax (as TRACOS load limit is 120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
Infinite auto-retry nrtry short to gnd
ADM - ISET Added resistor footprints for v2, put 0R for 10A limit like in v1.
This allows the chip to survive an overcurrent fault for Xms before going into fault. t_{itimer(ms)} = (C_{itimer(nF)} * deltaV_{itimer(V)}) / I_{itimer (uA)} deltaV_timer = 0.98V itimer = 2.1uA --> t_{itimer} = 0.4667*C_{itimer(nF)} tITIMER = 5 ms -> allows moderate transient overcurrent pulses wi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
ADM - TIMER 500nF gives 47ms, just enough to pass startup with some margin while being under SOA with enough margin to cover for temperature derating
